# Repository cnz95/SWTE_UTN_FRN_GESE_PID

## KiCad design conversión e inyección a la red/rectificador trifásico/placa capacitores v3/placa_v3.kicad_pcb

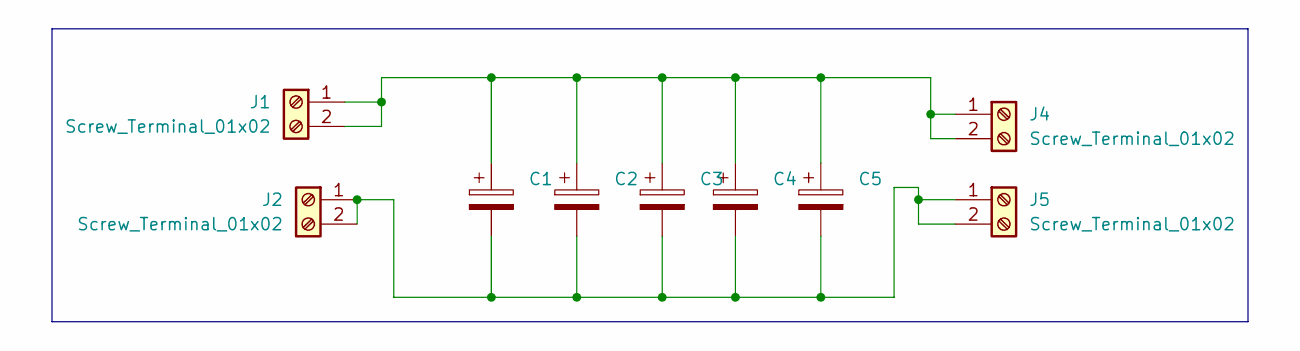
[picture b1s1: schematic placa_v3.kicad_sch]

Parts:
C1, C2, C3, C4, C5: C_Polarized; CP_Radial_D22.0mm_P10.00mm_SnapIn
J1, J2, J4, J5: Screw_Terminal_01x02; TerminalBlock_Phoenix_MKDS-1,5-2-5.08_1x02_P5.08mm_Horizont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

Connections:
unnamed: C1.1, C2.1, C3.1, C4.1, C5.1, J1.1, J1.2, J4.1, J4.2
unnamed: C1.2, C2.2, C3.2, C4.2, C5.2, J2.1, J2.2, J5.1, J5.2

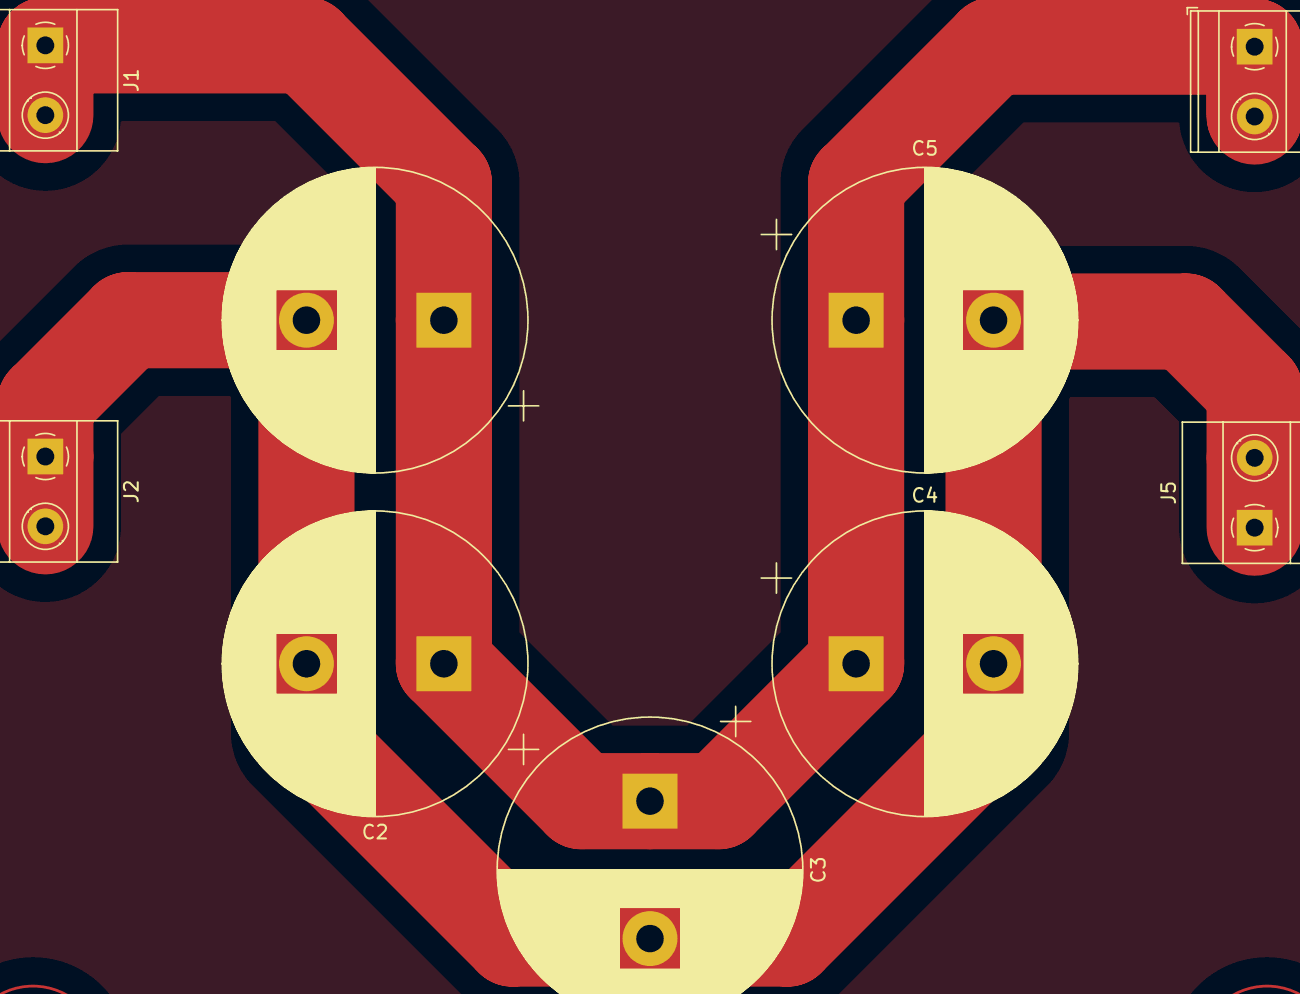
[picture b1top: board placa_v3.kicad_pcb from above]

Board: 2 copper layers, 9 parts (0 on the bottom side), 2 nets.
